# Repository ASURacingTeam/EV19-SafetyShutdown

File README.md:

# ASU Racing Team Formula Students Electric 2019 Safety and Shutdown System

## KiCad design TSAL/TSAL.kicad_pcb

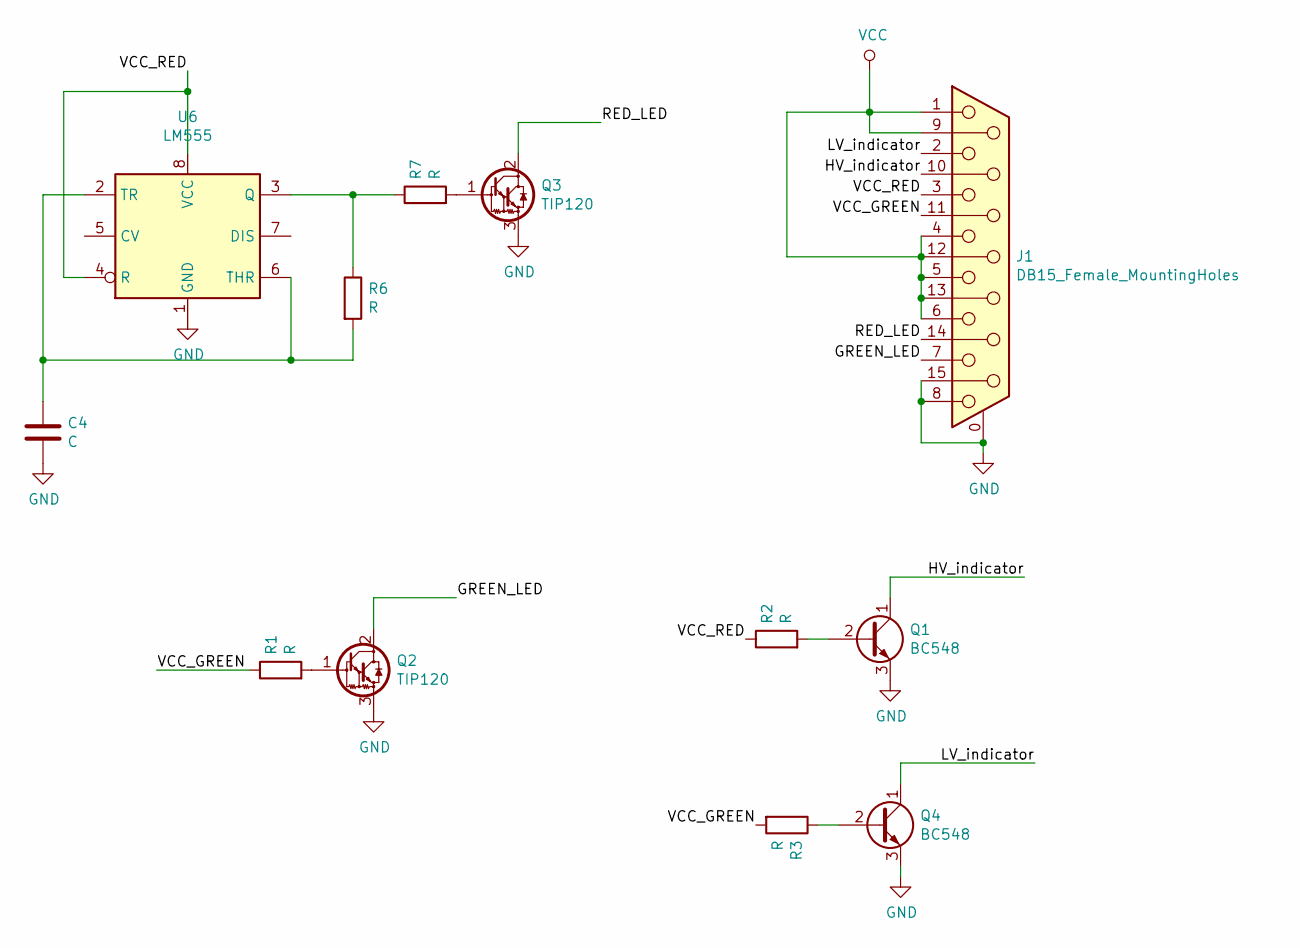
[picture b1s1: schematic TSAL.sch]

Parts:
C4: C; CP_Radial_D7.5mm_P2.50mm
J1: DB15_Female_MountingHoles; DSUB-15_Female_Horizontal_P2.77x2.84mm_EdgePinOffset7.70mm_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
Q1, Q4: BC548; TO-92_Inline
Q2, Q3: TIP120; TO-220-3_Horizontal_TabDown
R1, R2, R3, R6, R7: R; R_Axial_DIN0207_L6.3mm_D2.5mm_P7.62mm_Horizontal
U6: LM555; DIP-8_W7.62mm_Socket_LongPads

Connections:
/GREEN_LED: J1.7, Q2.2 (C)
/HV_indicator: J1.10, Q1.1 (C)
/LV_indicator: J1.2, Q4.1 (C)
/RED_LED: J1.14, Q3.2 (C)
/VCC_GREEN: J1.11 (P111), R1.1, R3.2
/VCC_RED: J1.3, R2.1, U6.4 (R), U6.8 (VCC)
GND: C4.2, J1.0 (PAD), J1.8, J1.15, Q1.3 (E), Q2.3 (E), Q3.3 (E), Q4.3 (E), U6.1 (GND)
unnamed: C4.1, R6.2, U6.2 (TR), U6.6 (THR)
unnamed: Q1.2 (B), R2.2
unnamed: Q2.1 (B), R1.2
unnamed: Q3.1 (B), R7.2
unnamed: Q4.2 (B), R3.1
unnamed: R6.1, R7.1, U6.3 (Q)
VCC: J1.1, J1.4, J1.5, J1.6, J1.9, J1.12, J1.13

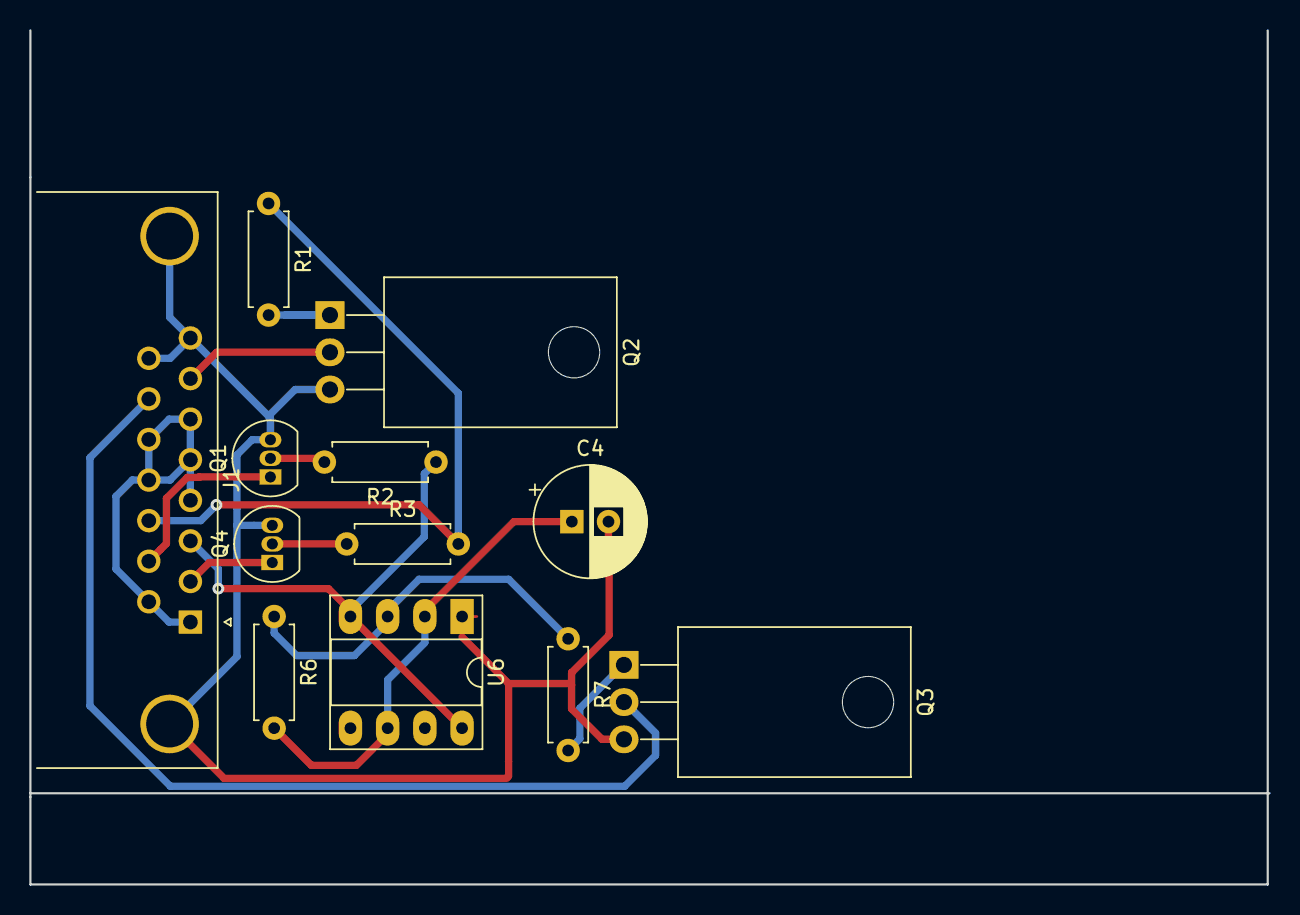
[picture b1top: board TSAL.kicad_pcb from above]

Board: 2 copper layers, 84.6 x 58.3 mm, 12 parts (0 on the bottom side), 14 nets.

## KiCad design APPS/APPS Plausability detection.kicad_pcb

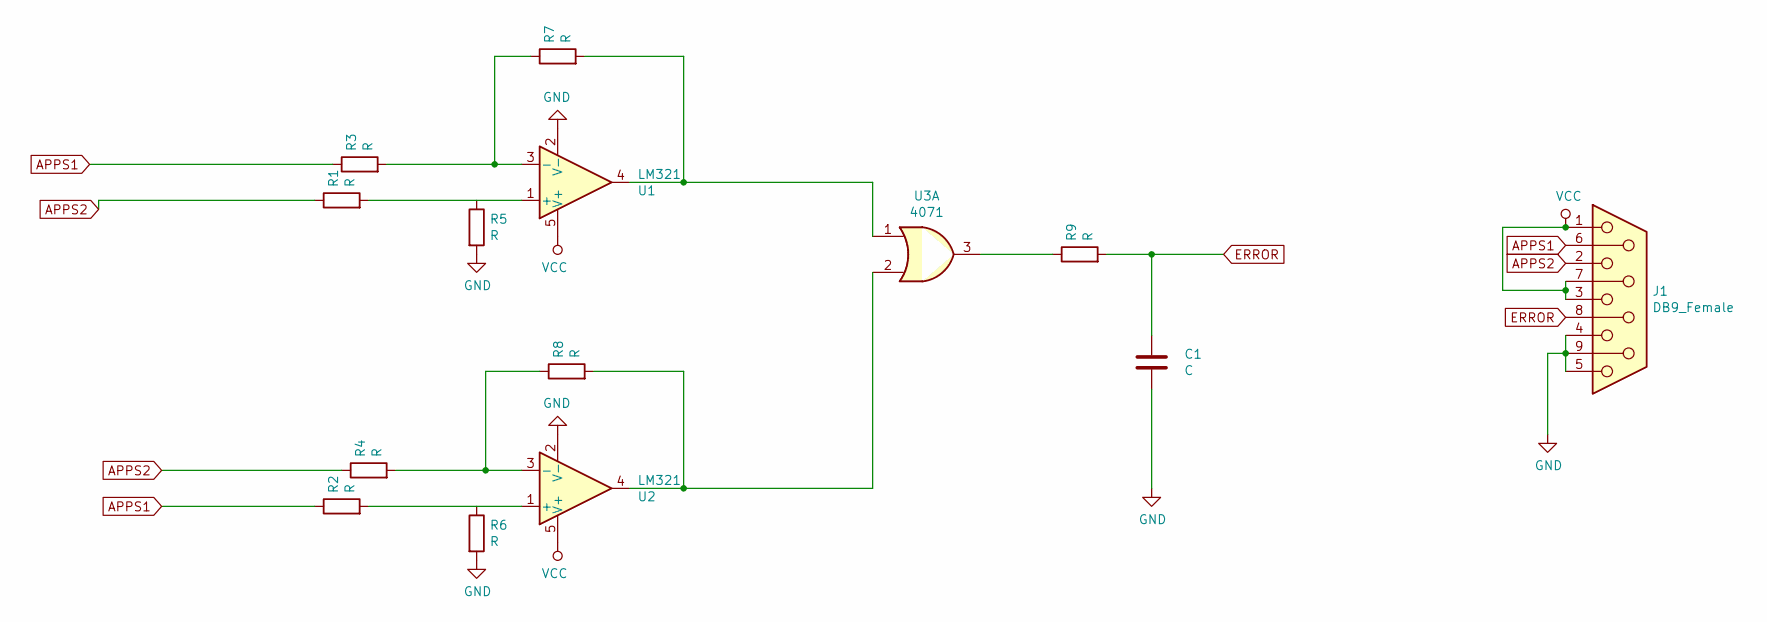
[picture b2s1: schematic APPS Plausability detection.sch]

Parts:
C1: C; CP_Radial_D7.5mm_P2.50mm
J1: DB9_Female; DSUB-9_Female_Horizontal_P2.77x2.84mm_EdgePinOffset7.70mm_H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
R1, R2, R3, R4, R5, R6, R7, R8, R9: R; R_Axial_DIN0207_L6.3mm_D2.5mm_P7.62mm_Horizontal
U1, U2: LM321; DIP-6_W7.62mm_Socket
U3: 4071; DIP-14_W7.62mm_Socket_LongPads

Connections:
APPS1: J1.6, R2.1, R3.1
APPS2: J1.2, R1.1, R4.1
ERROR: C1.1, J1.8, R9.2
GND: C1.2, J1.4, J1.5, J1.9, R5.2, R6.2, U1.2 (V-), U2.2 (V-)
unnamed: R1.2, R5.1, U1.1 (+)
unnamed: R2.2, R6.1, U2.1 (+)
unnamed: R3.2, R7.1, U1.3 (-)
unnamed: R4.2, R8.1, U2.3 (-)
unnamed: R7.2, U1.4, U3.1
unnamed: R8.2, U2.4, U3.2
unnamed: R9.1, U3.3
VCC: J1.1, J1.3, J1.7, U1.5 (V+), U2.5 (V+)

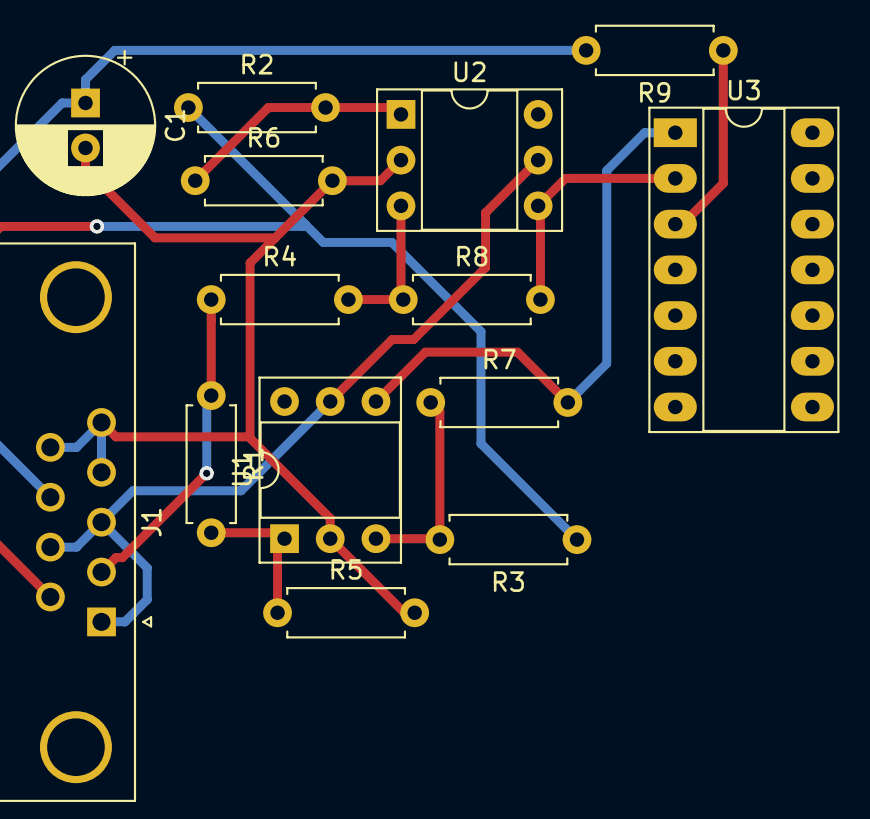
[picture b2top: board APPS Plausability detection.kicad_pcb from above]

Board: 2 copper layers, 14 parts (0 on the bottom side), 12 nets.

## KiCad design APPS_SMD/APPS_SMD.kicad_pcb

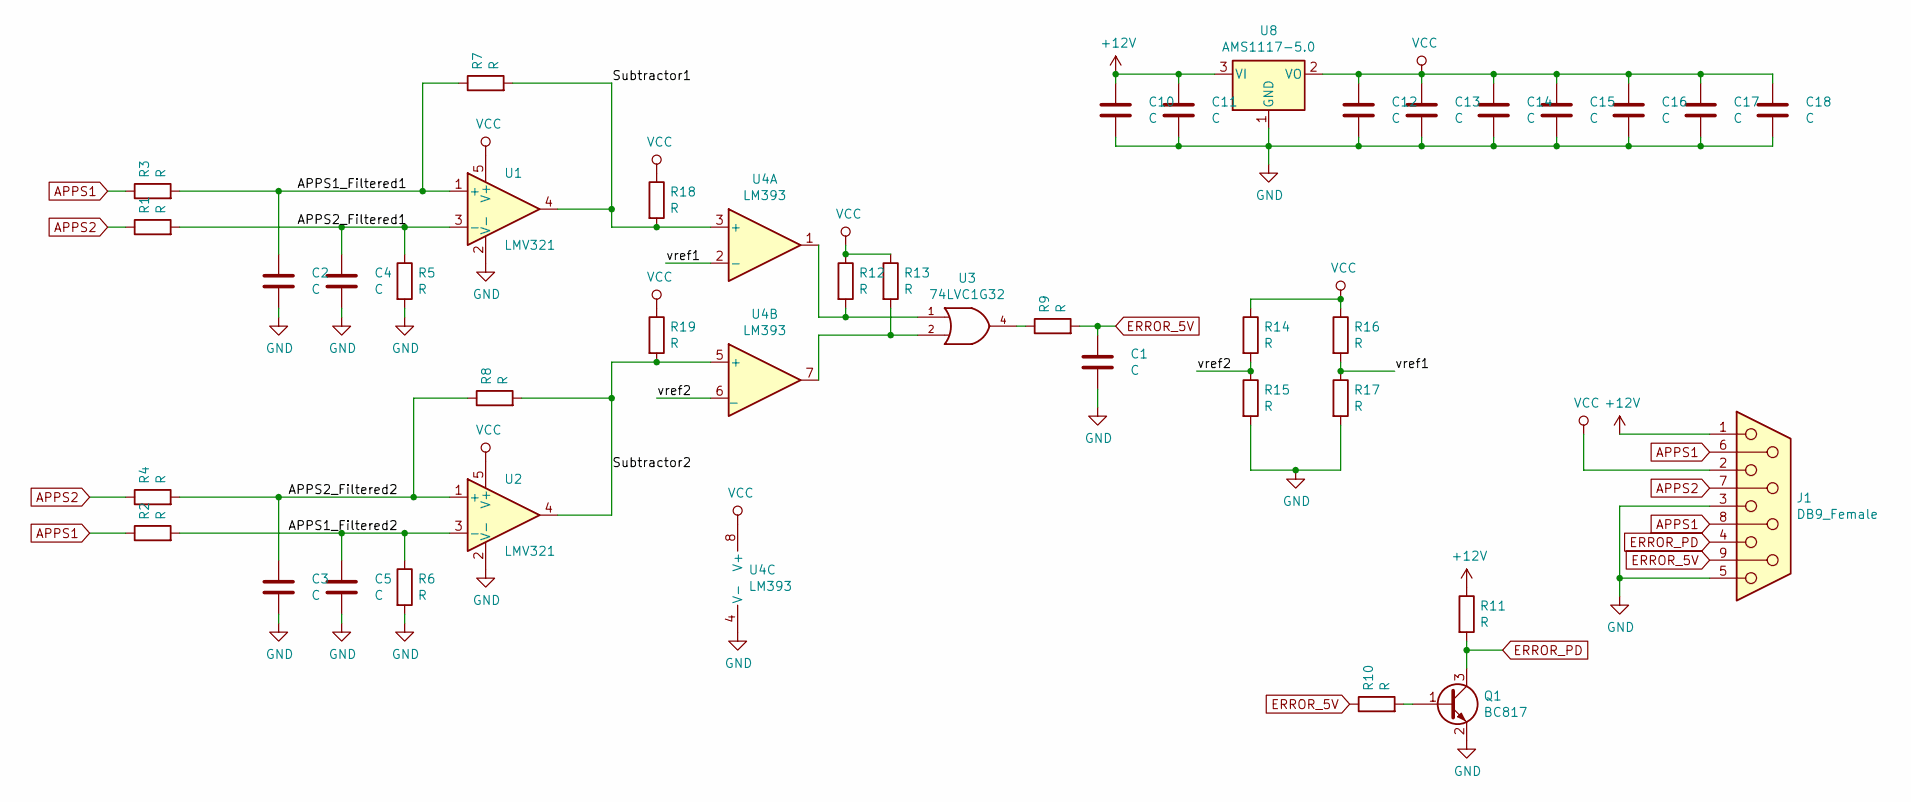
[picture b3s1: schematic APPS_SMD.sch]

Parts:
C1, C2, C3, C4, C5, C11, C12, C14, C15, C16, C17, C18: C; C_0805_2012Metric_Pad1.15x1.40mm_HandSolder
C10, C13: C; C_1206_3216Metric_Pad1.42x1.75mm_HandSolder
J1: DB9_Female; DSUB-9_Female_Horizontal_P2.77x2.84mm_EdgePinOffset4.94mm_H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
Q1: BC817; SOT-23
R1, R2, R3, R4, R5, R6, R7, R8, R9, R10, R11, R12, R13, R14, R15, R16, R17, R18, R19: R; R_0805_2012Metric_Pad1.15x1.40mm_HandSolder
U1, U2: LMV321; SOT-23-5
U3: 74LVC1G32; SOT-23-5
U4: LM393; SOIC-8_3.9x4.9mm_P1.27mm
U8: AMS1117-5.0; SOT-223-3_TabPin2

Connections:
+12V: C10.1, C11.1, J1.1, R11.1, U8.3 (VI)
/APPS1_Filtered1: C2.1, R3.2, R7.1, U1.1 (+)
/APPS1_Filtered2: C5.1, R2.2, R6.1, U2.3 (-)
/APPS2_Filtered1: C4.1, R1.2, R5.1, U1.3 (-)
/APPS2_Filtered2: C3.1, R4.2, R8.1, U2.1 (+)
/Subtractor1: R7.2, R18.2, U1.4, U4.3 (+)
/Subtractor2: R8.2, R19.2, U2.4, U4.5 (+)
/vref1: R16.2, R17.1, U4.2 (-)
/vref2: R14.2, R15.1, U4.6 (_)
APPS1: J1.6, J1.8, R2.1, R3.1
APPS2: J1.7, R1.1, R4.1
ERROR_5V: C1.1, J1.9, R9.2, R10.1
ERROR_PD: J1.4, Q1.3 (C), R11.2
GND: C1.2, C2.2, C3.2, C4.2, C5.2, C10.2, C11.2, C12.2, C13.2, C14.2, C15.2, C16.2, C17.2, C18.2, J1.3, J1.5, Q1.2 (E), R5.2, R6.2, R15.2, R17.2, U1.2 (V-), U2.2 (V-), U3.3 (GND), U4.4 (V-), U8.1 (GND)
unnamed: Q1.1 (B), R10.2
unnamed: R9.1, U3.4
unnamed: R12.2, U3.1, U4.1
unnamed: R13.2, U3.2, U4.7
VCC: C12.1, C13.1, C14.1, C15.1, C16.1, C17.1, C18.1, J1.2, R12.1, R13.1, R14.1, R16.1, R18.1, R19.1, U1.5 (V+), U2.5 (V+), U3.5 (VCC), U4.8 (V+), U8.2 (VO)

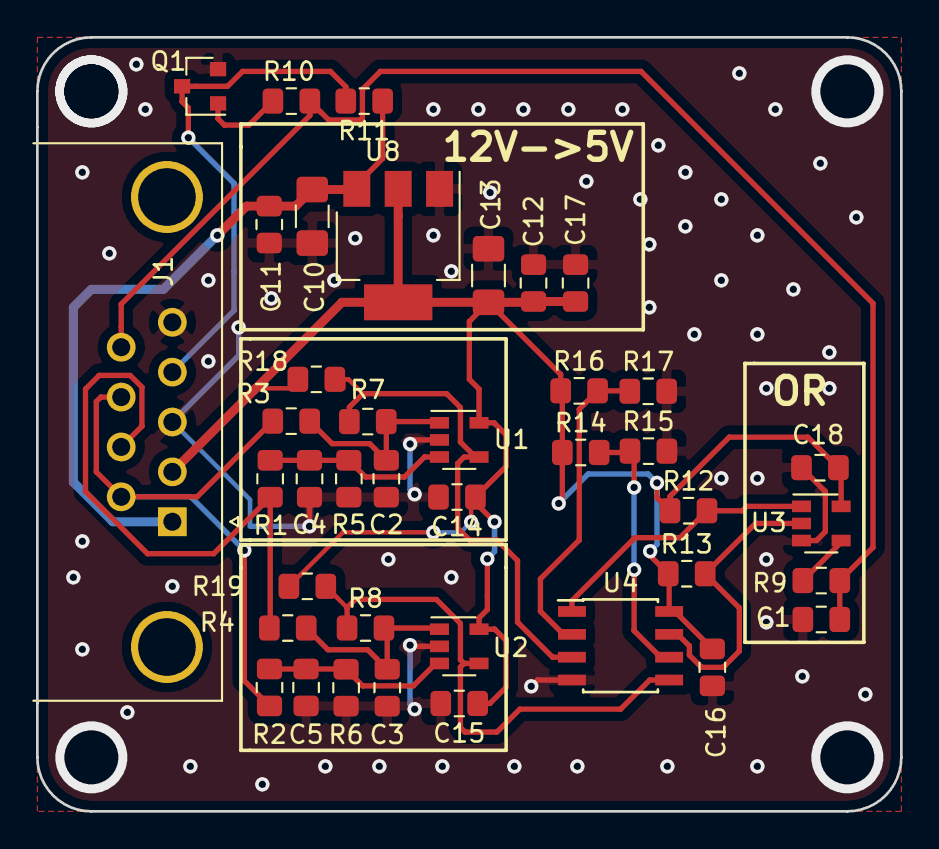
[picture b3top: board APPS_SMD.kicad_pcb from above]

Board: 2 copper layers, 48.0 x 43.0 mm, 40 parts (0 on the bottom side), 19 nets.

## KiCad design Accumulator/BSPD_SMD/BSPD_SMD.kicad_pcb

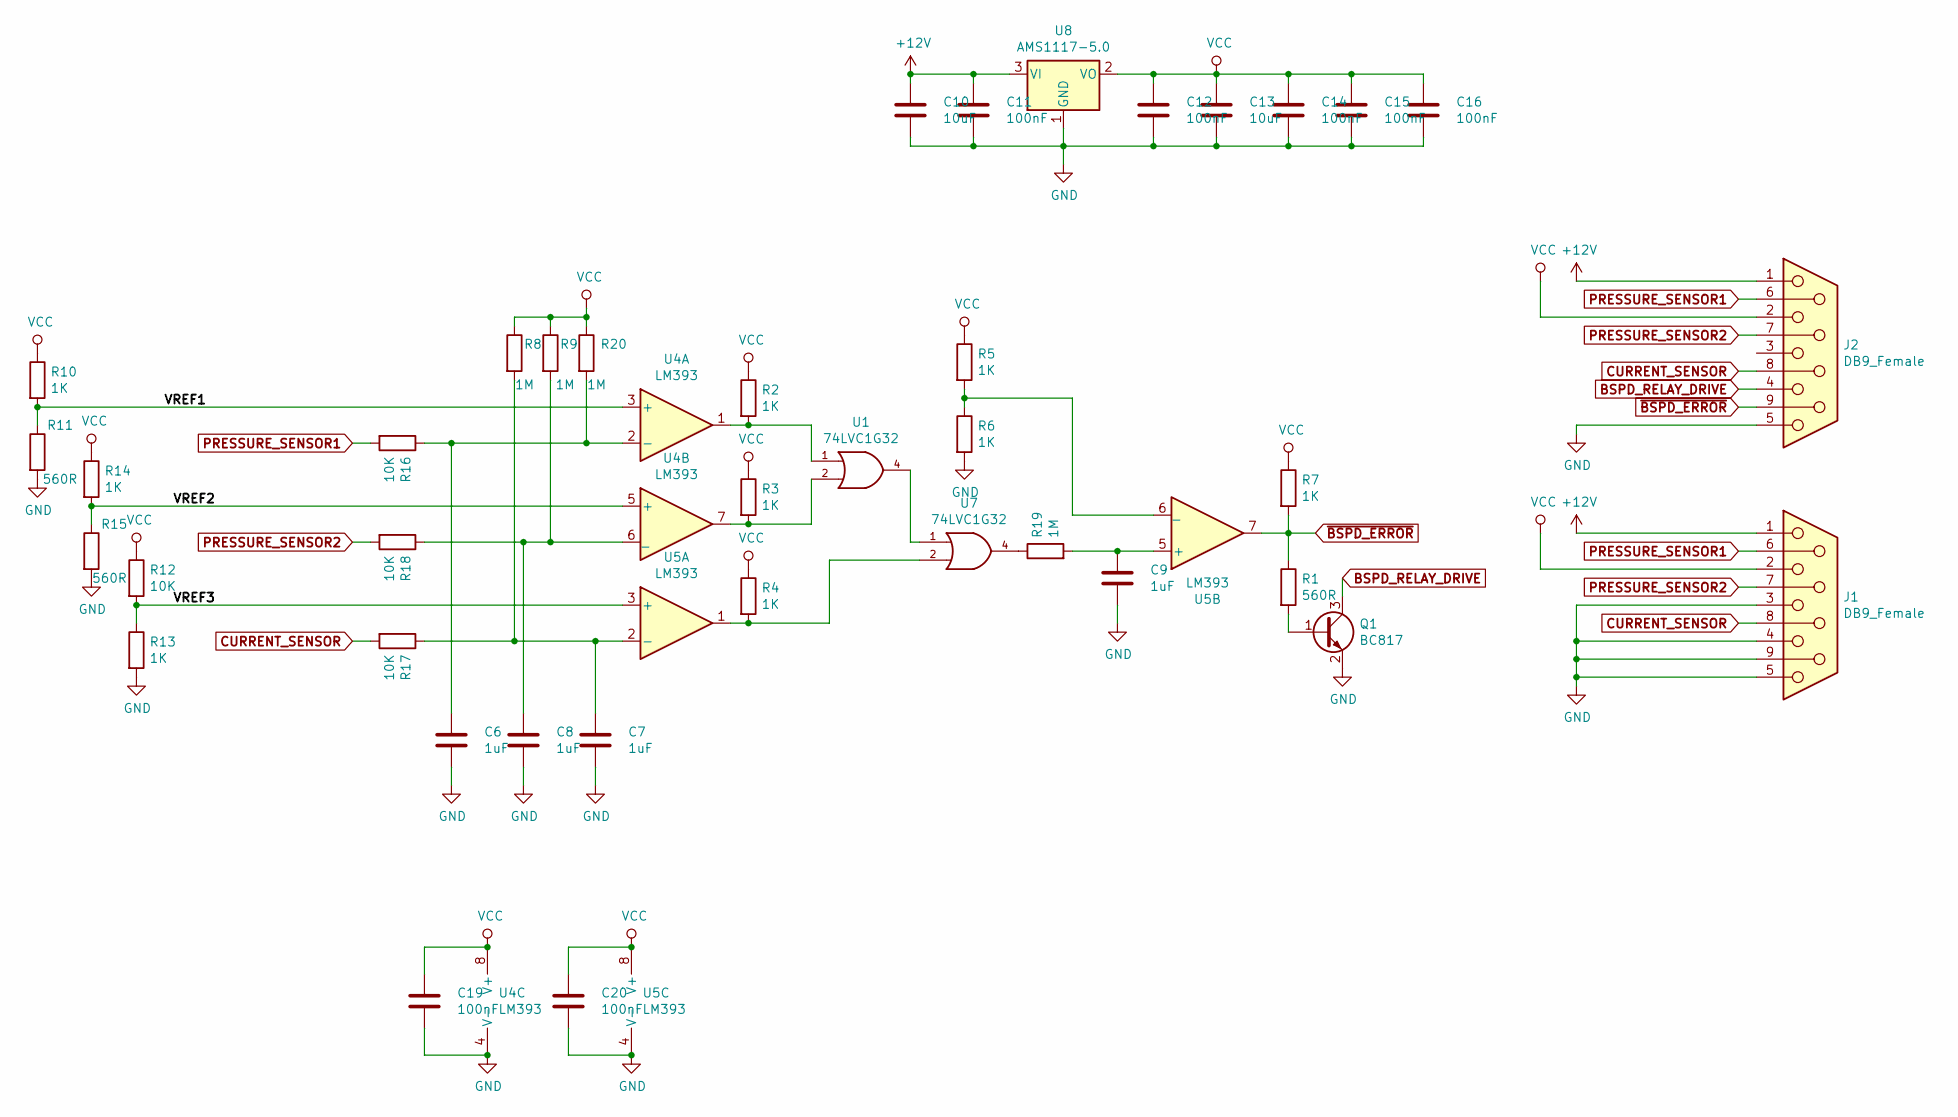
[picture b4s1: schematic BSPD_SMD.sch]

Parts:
C6, C7, C8, C9: 1uF; C_0805_2012Metric_Pad1.15x1.40mm_HandSolder
C10, C13: 10uF; C_1206_3216Metric_Pad1.42x1.75mm_HandSolder
C11, C12, C14, C15, C16, C19, C20: 100nF; C_0805_2012Metric_Pad1.15x1.40mm_HandSolder
J1, J2: DB9_Female; DSUB-9_Female_Horizontal_P2.77x2.84mm_EdgePinOffset4.94mm_H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
Q1: BC817; SOT-23
R1, R11, R15: 560R; R_0805_2012Metric_Pad1.15x1.40mm_HandSolder
R2, R3, R4, R5, R6, R7, R10, R13, R14: 1K; R_0805_2012Metric_Pad1.15x1.40mm_HandSolder
R8, R9, R19, R20: 1M; R_0805_2012Metric_Pad1.15x1.40mm_HandSolder
R12, R16, R17, R18: 10K; R_0805_2012Metric_Pad1.15x1.40mm_HandSolder
U1, U7: 74LVC1G32; SOT-23-5
U4, U5: LM393; SOIC-8_3.9x4.9mm_P1.27mm
U8: AMS1117-5.0; SOT-223-3_TabPin2

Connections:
+12V: C10.1, C11.1, J1.1, J2.1, U8.3 (VI)
/VREF1: R10.2, R11.1, U4.3 (+)
/VREF2: R14.2, R15.1, U4.5 (+)
/VREF3: R12.2, R13.1, U5.3 (+)
BSPD_RELAY_DRIVE: J2.4, Q1.3 (C)
CURRENT_SENSOR: J1.8, J2.8, R17.2
GND: C6.2, C7.2, C8.2, C9.2, C10.2, C11.2, C12.2, C13.2, C14.2, C15.2, C16.2, C19.2, C20.2, J1.3, J1.4, J1.5, J1.9, J2.5, Q1.2 (E), R6.2, R11.2, R13.2, R15.2, U1.3 (GND), U4.4 (V-), U5.4 (V-), U7.3 (GND), U8.1 (GND)
unnamed: C6.1, R16.1, R20.2, U4.2 (-)
unnamed: C7.1, R8.2, R17.1, U5.2 (-)
unnamed: C8.1, R9.2, R18.1, U4.6 (_)
unnamed: C9.1, R19.2, U5.5 (+)
unnamed: Q1.1 (B), R1.2
unnamed: R2.2, U1.1, U4.1
unnamed: R3.2, U1.2, U4.7
unnamed: R4.2, U5.1, U7.2
unnamed: R5.2, R6.1, U5.6 (_)
unnamed: R19.1, U7.4
unnamed: U1.4, U7.1
PRESSURE_SENSOR1: J1.6, J2.6, R16.2
PRESSURE_SENSOR2: J1.7, J2.7, R18.2
VCC: C12.1, C13.1, C14.1, C15.1, C16.1, C19.1, C20.1, J1.2, J2.2, R2.1, R3.1, R4.1, R5.1, R7.1, R8.1, R9.1, R10.1, R12.1, R14.1, R20.1, U1.5 (VCC), U4.8 (V+), U5.8 (V+), U7.5 (VCC), U8.2 (VO)
~BSPD_ERROR: J2.9, R1.1, R7.2, U5.7

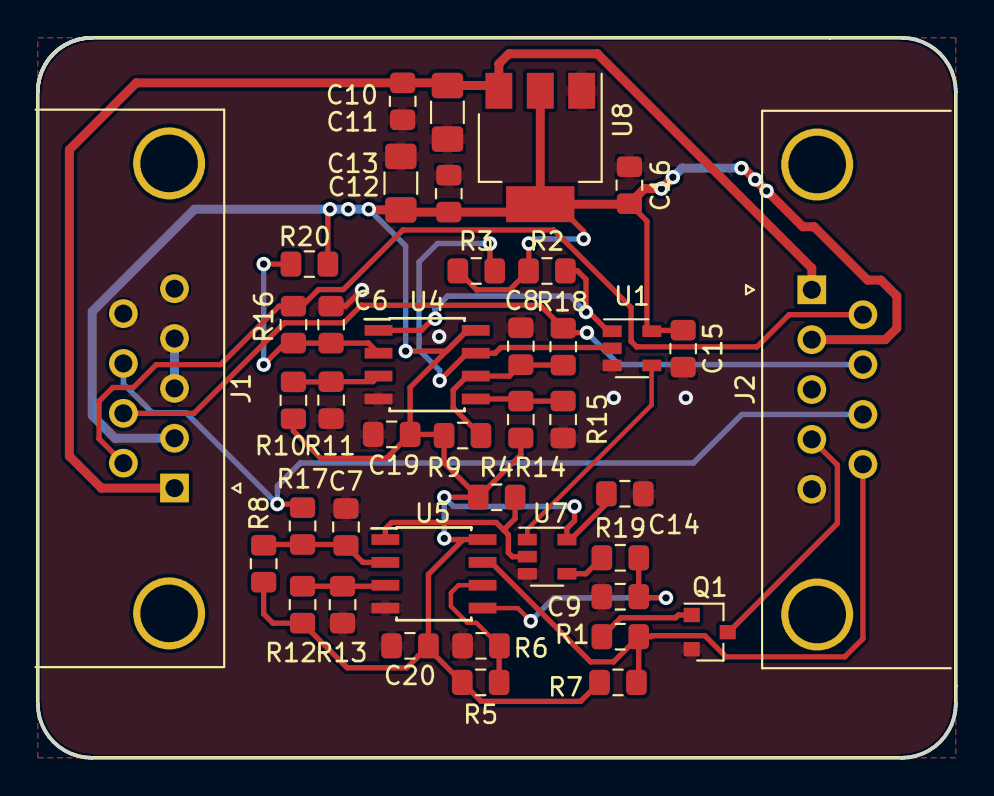
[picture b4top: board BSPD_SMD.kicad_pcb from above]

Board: 2 copper layers, 51.0 x 40.0 mm, 41 parts (0 on the bottom side), 22 nets.

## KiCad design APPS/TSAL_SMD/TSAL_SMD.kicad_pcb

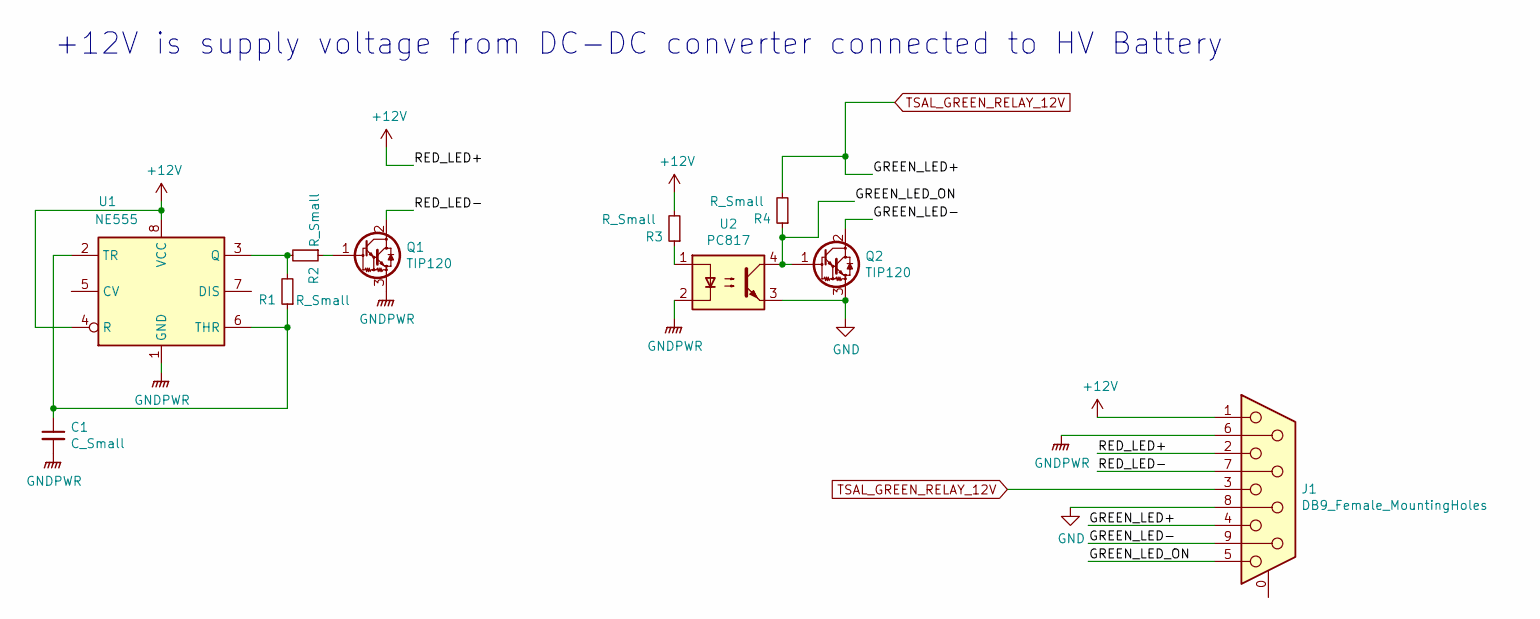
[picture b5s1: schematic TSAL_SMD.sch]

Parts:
C1: C_Small; CP_Radial_D8.0mm_P2.50mm
J1: DB9_Female_MountingHoles; DSUB-9_Female_Horizontal_P2.77x2.84mm_EdgePinOffset4.94mm_H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
Q1, Q2: TIP120; TO-220-3_Vertical
R1, R2, R3, R4: R_Small; R_Axial_DIN0411_L9.9mm_D3.6mm_P12.70mm_Horizontal
U1: NE555; DIP-8_W7.62mm_Socket_LongPads
U2: PC817; DIP-4_W7.62mm

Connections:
+12L: J1.3, J1.4, R4.2
+12V: J1.1, J1.2, R3.2, U1.4 (R), U1.8 (VCC)
/GREEN_LED-: J1.9, Q2.2 (C)
/GREEN_LED_ON: J1.5, Q2.1 (B), R4.1, U2.4
/RED_LED-: J1.7, Q1.2 (C)
GND: J1.8, Q2.3 (E), U2.3
GNDPWR: C1.2, J1.6, Q1.3 (E), U1.1 (GND), U2.2
unnamed: C1.1, R1.1, U1.2 (TR), U1.6 (THR)
unnamed: Q1.1 (B), R2.1
unnamed: R1.2, R2.2, U1.3 (Q)
unnamed: R3.1, U2.1

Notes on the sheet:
+12V is supply voltage from DC-DC converter connected to HV Battery

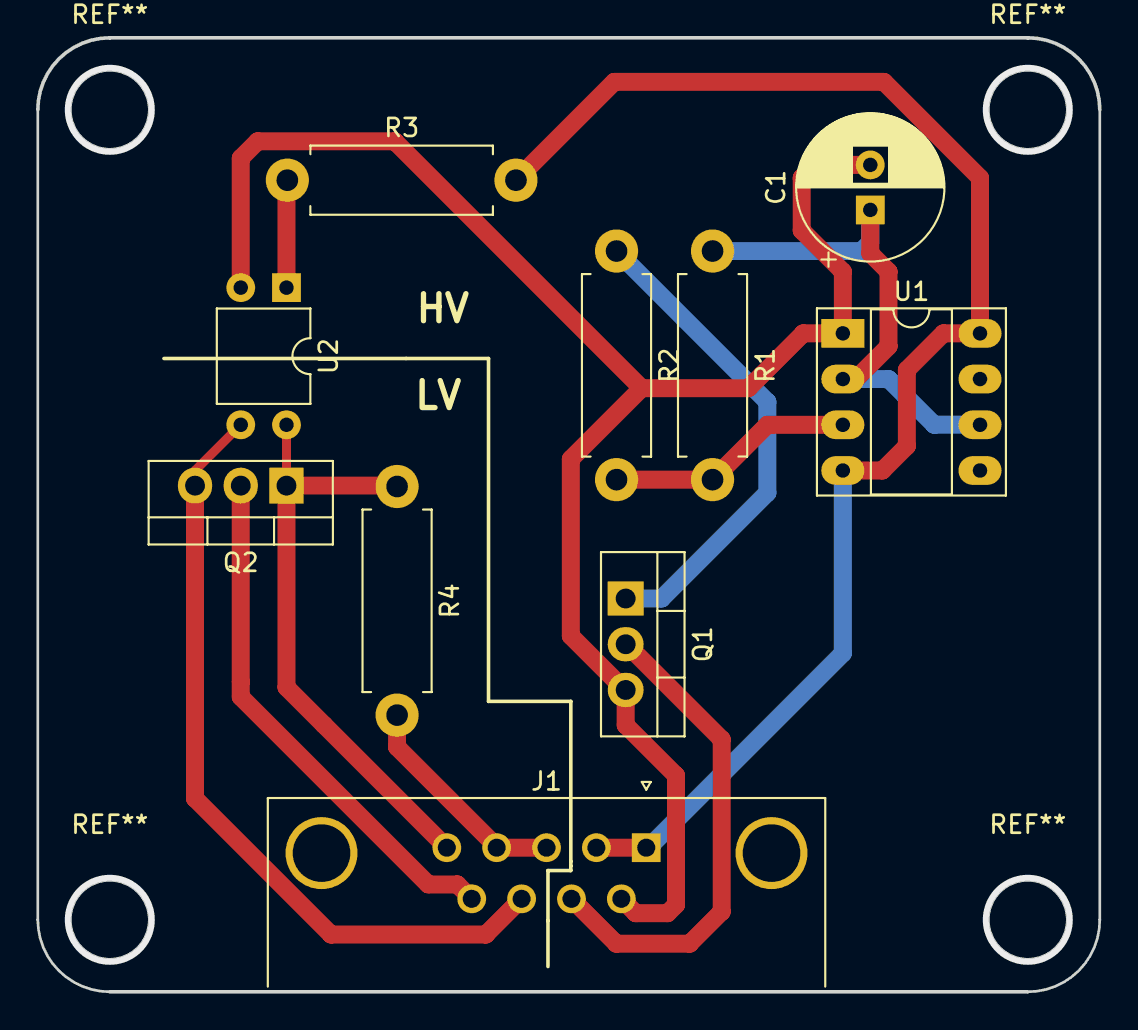
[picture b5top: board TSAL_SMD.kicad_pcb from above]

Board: 2 copper layers, 59.0 x 53.0 mm, 10 parts (0 on the bottom side), 11 nets.
